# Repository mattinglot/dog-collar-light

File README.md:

# Dog Collar Light
Developed by Matt Inglot

## Overview
This is the LED dog collar light PCB and firmware that I built for my dog Joey and a few of his friends.

Overview of the Light:
https://youtu.be/FvTPfEKD1Q0

Details about the PCB Design:
https://youtu.be/JEl7wfQJ-MM

## License
* The firmware source code is licensed under the MIT license.
* The PCB design is licensed under the Creative Commons Attribution Share Alike 4.0 International license.

See the LICENSE file in each folder of the project for the applicable license.

## Share Your Creations!
If you end up building one of these lights, I would really love to know! Please leave a comment on https://youtu.be/FvTPfEKD1Q0 with a link to your work.

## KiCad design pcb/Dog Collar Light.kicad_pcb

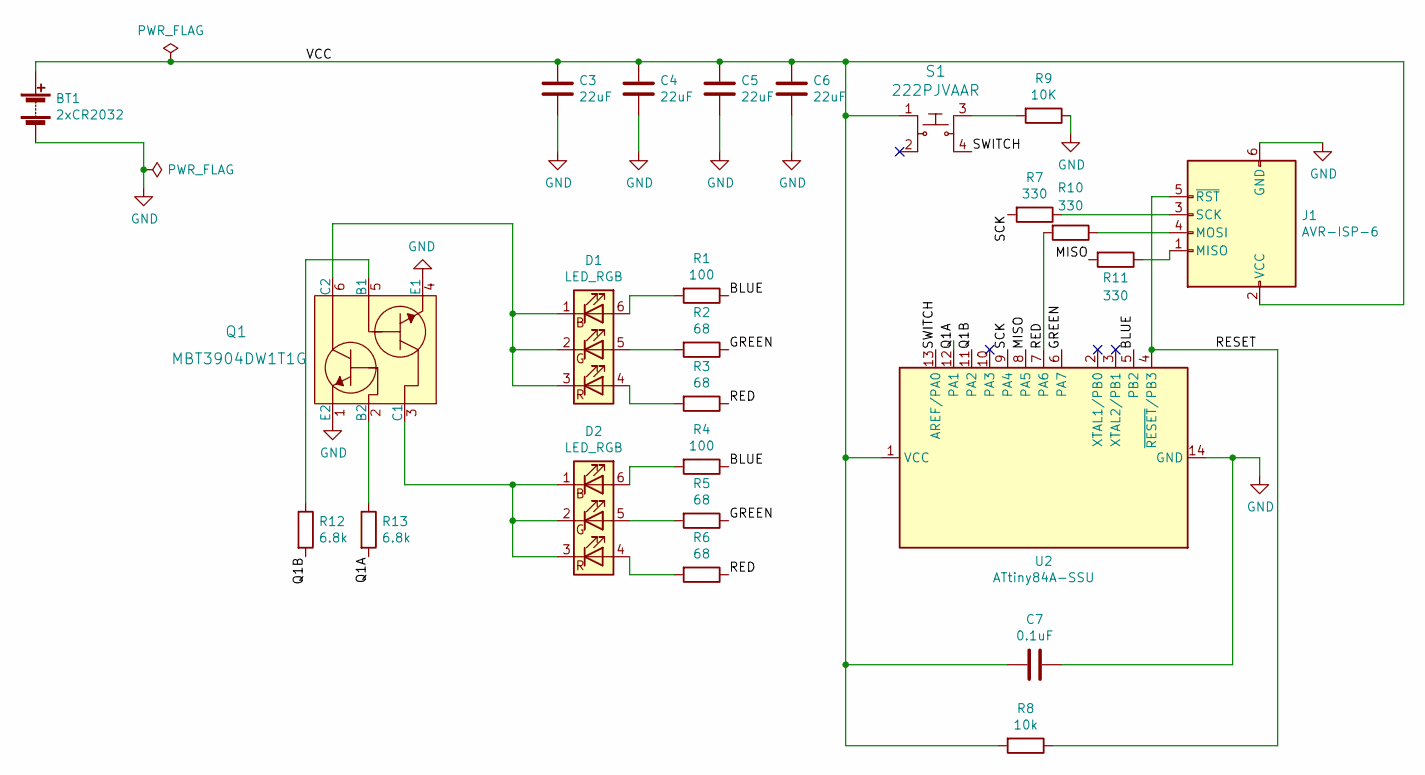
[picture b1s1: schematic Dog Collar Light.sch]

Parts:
BT1: 2xCR2032; BatteryHolder_Keystone_3024
C3, C4, C5, C6: 22uF; C_0805_2012Metric_Pad1.15x1.40mm_HandSolder
C7: 0.1uF; C_0805_2012Metric_Pad1.15x1.40mm_HandSolder
D1, D2: LED_RGB; LED_Cree-SLV6A
J1: AVR-ISP-6; PinHeader_2x03_P2.54mm_Vertical
Q1: MBT3904DW1T1G; SOT-363; MPN MBT3904DW1T1G; Digi-Key_PN MBT3904DW1T1GOSCT-ND
R1, R4: 100; R_0805_2012Metric_Pad1.15x1.40mm_HandSolder
R2, R3, R5, R6: 68; R_0805_2012Metric_Pad1.15x1.40mm_HandSolder
R7, R10, R11: 330; R_0805_2012Metric_Pad1.15x1.40mm_HandSolder
R8: 10k; R_0805_2012Metric_Pad1.15x1.40mm_HandSolder
R9: 10K; R_0805_2012Metric_Pad1.15x1.40mm_HandSolder
R12, R13: 6.8k; R_0805_2012Metric_Pad1.15x1.40mm_HandSolder
S1: 222PJVAAR; Switch_222PJVAAR; MPN 1825910-6; Digi-Key_PN 450-1650-ND
U2: ATtiny84A-SSU; SOIC-14_3.9x8.7mm_P1.27mm

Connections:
/BLUE: R1.1, R4.1, U2.5 (PB2)
/GREEN: R2.1, R5.1, U2.6 (PA7)
/MISO: R11.2, U2.8 (PA5)
/Q1A: R13.2, U2.12 (PA1)
/Q1B: R12.2, U2.11 (PA2)
/RED: R3.1, R6.1, R10.2, U2.7 (PA6)
/SCK: R7.2, U2.9 (PA4)
/SWITCH: S1.4, U2.13 (AREF/PA0)
/VCC: BT1.1 (+), C3.1, C4.1, C5.1, C6.1, C7.2, J1.2 (VCC), R8.2, S1.1, U2.1 (VCC)
GND: BT1.2 (-), C3.2, C4.2, C5.2, C6.2, C7.1, J1.6 (GND), Q1.1 (E2), Q1.4 (E1), R9.1, U2.14 (GND)
unnamed: D1.1 (RK), D1.2 (GK), D1.3 (BK), Q1.6 (C2)
unnamed: D1.4 (BA), R3.2
unnamed: D1.5 (GA), R2.2
unnamed: D1.6 (RA), R1.2
unnamed: D2.1 (RK), D2.2 (GK), D2.3 (BK), Q1.3 (C1)
unnamed: D2.4 (BA), R6.2
unnamed: D2.5 (GA), R5.2
unnamed: D2.6 (RA), R4.2
unnamed: J1.1 (MISO), R11.1
unnamed: J1.3 (SCK), R7.1
unnamed: J1.4 (MOSI), R10.1
unnamed: J1.5 (~RST), R8.1, U2.4 (~RESET~/PB3)
unnamed: Q1.2 (B2), R13.1
unnamed: Q1.5 (B1), R12.1
unnamed: R9.2, S1.3

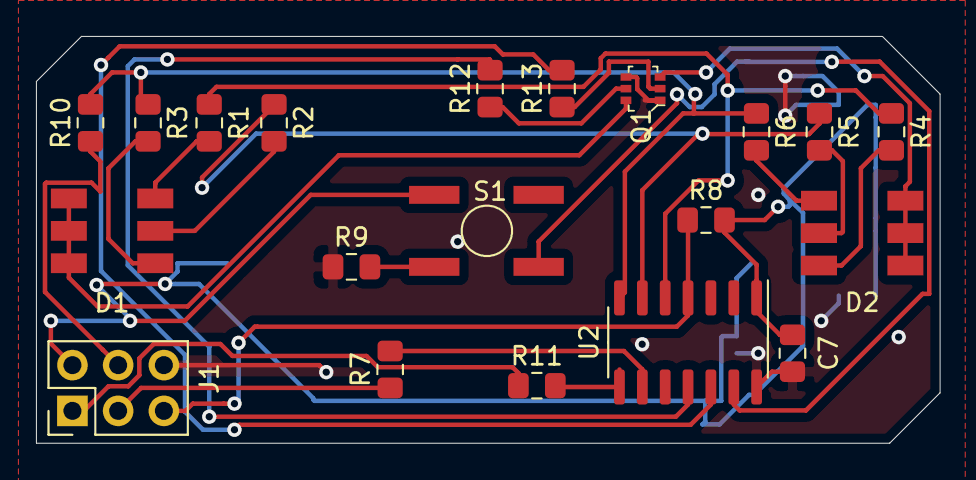
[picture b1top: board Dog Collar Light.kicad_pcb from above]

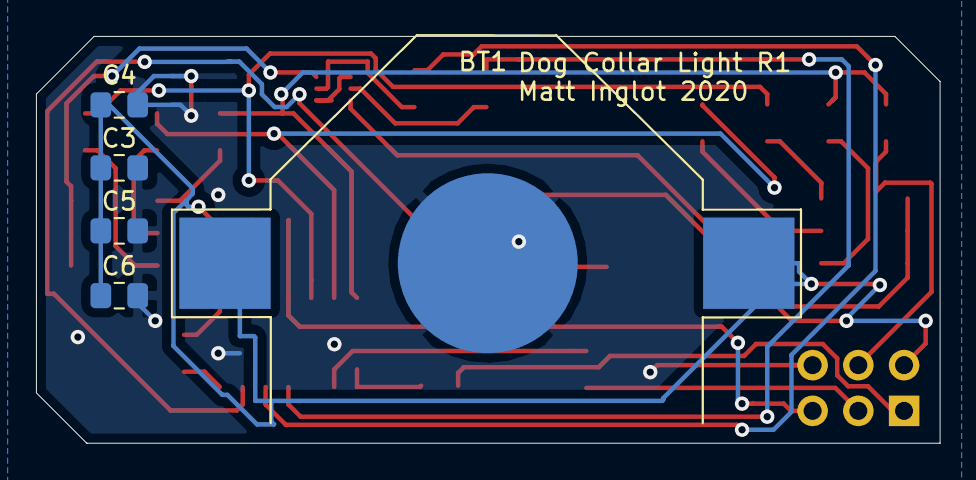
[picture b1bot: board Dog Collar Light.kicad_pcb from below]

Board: 2 copper layers, 50.2 x 22.6 mm, 25 parts (5 on the bottom side), 25 nets.

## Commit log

2021-01-30 Porting dog collar light code to github
2021-01-30 Added eeprom save so momentary loss of power doesn't cause light to turn off (eg dog shaking head causing battery to briefly lose contact)
    Also renamed main file to dog-collar-light.ino to match repo name.
2021-08-03 Removed some comments.
2021-11-07 Reorganized the project so that the source code is in its own folder.
2021-11-07 Added Kicad files.
2021-11-12 Updated recommended switch to one that fits case better. It is much shorter so you can squish the case more to turn on/off.
2021-11-12 Removed kicad .bak files.
2024-12-26 Added .gitignore

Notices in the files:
pcb/Dog Collar Light.sch:
Licensed under CC-BY-SA-4.0
